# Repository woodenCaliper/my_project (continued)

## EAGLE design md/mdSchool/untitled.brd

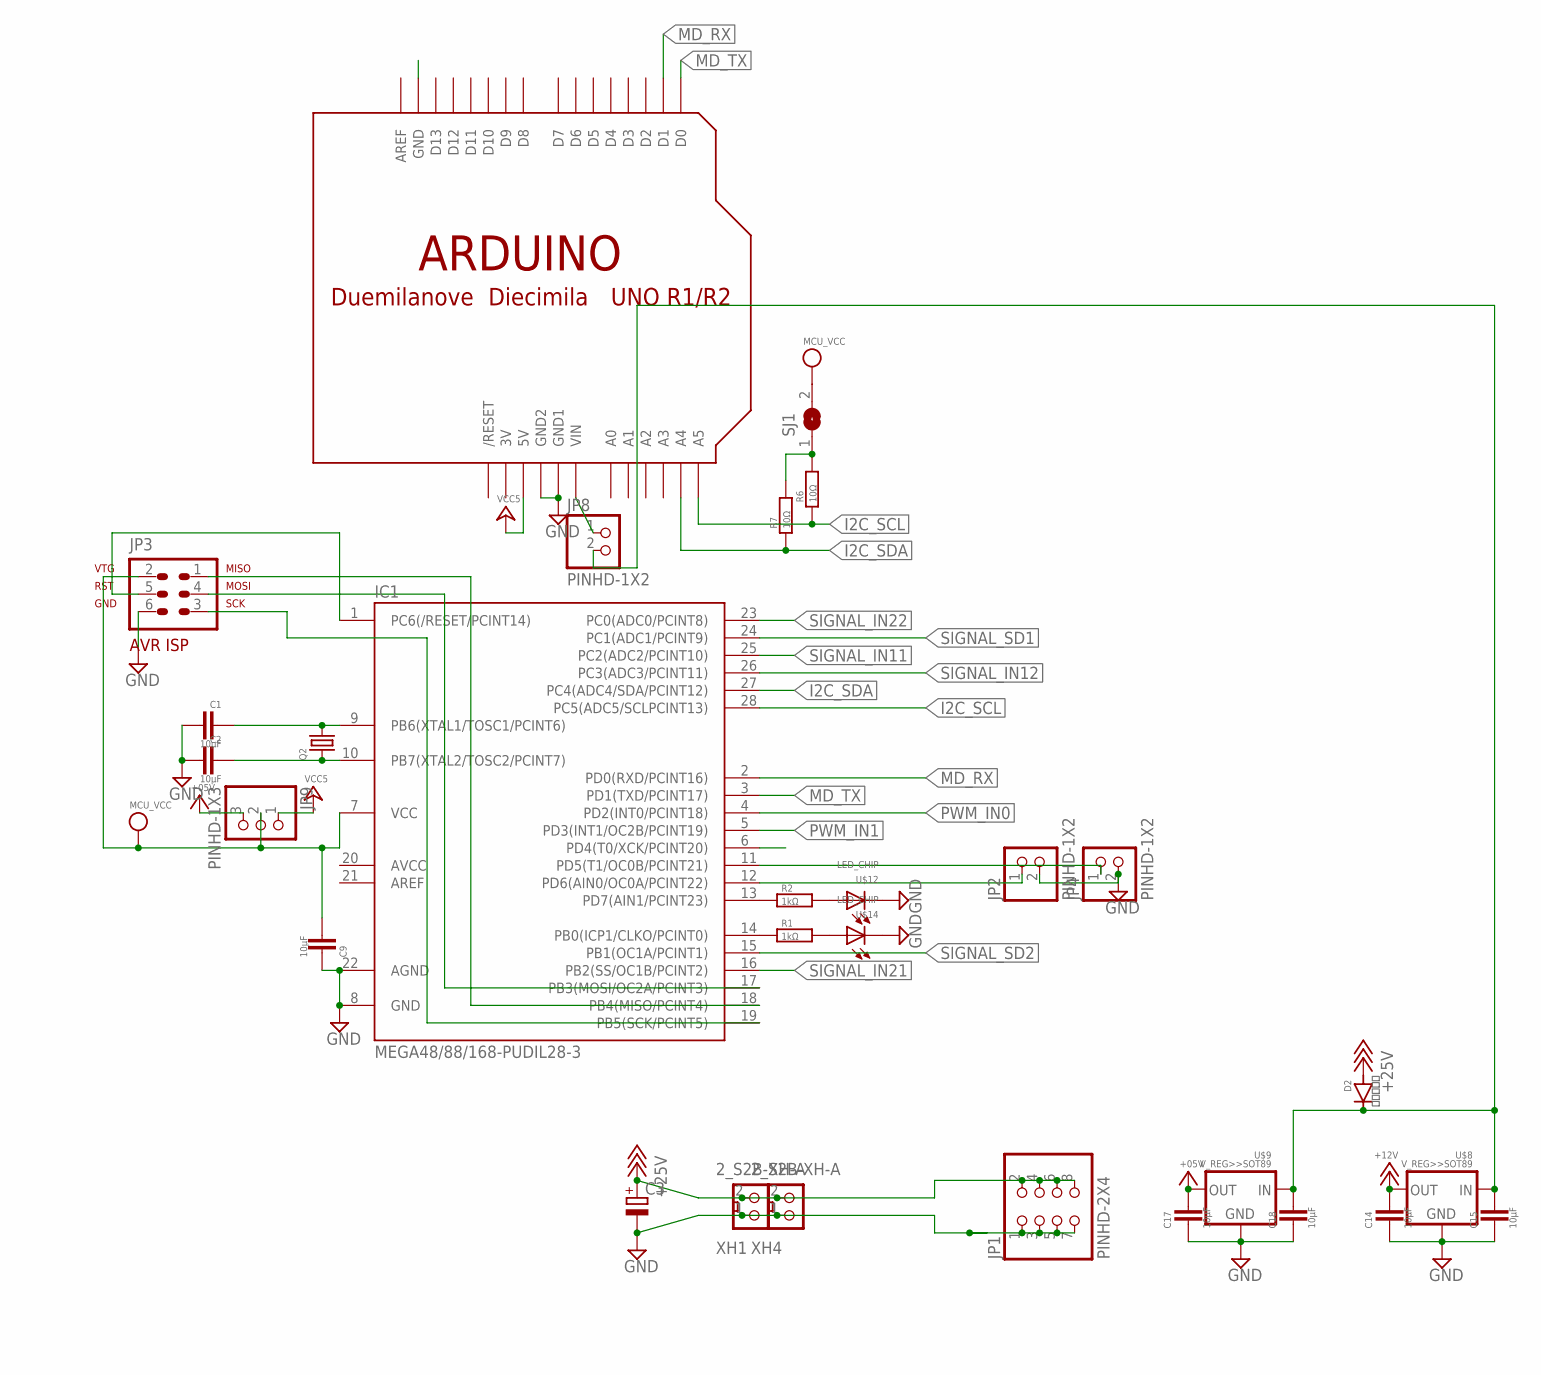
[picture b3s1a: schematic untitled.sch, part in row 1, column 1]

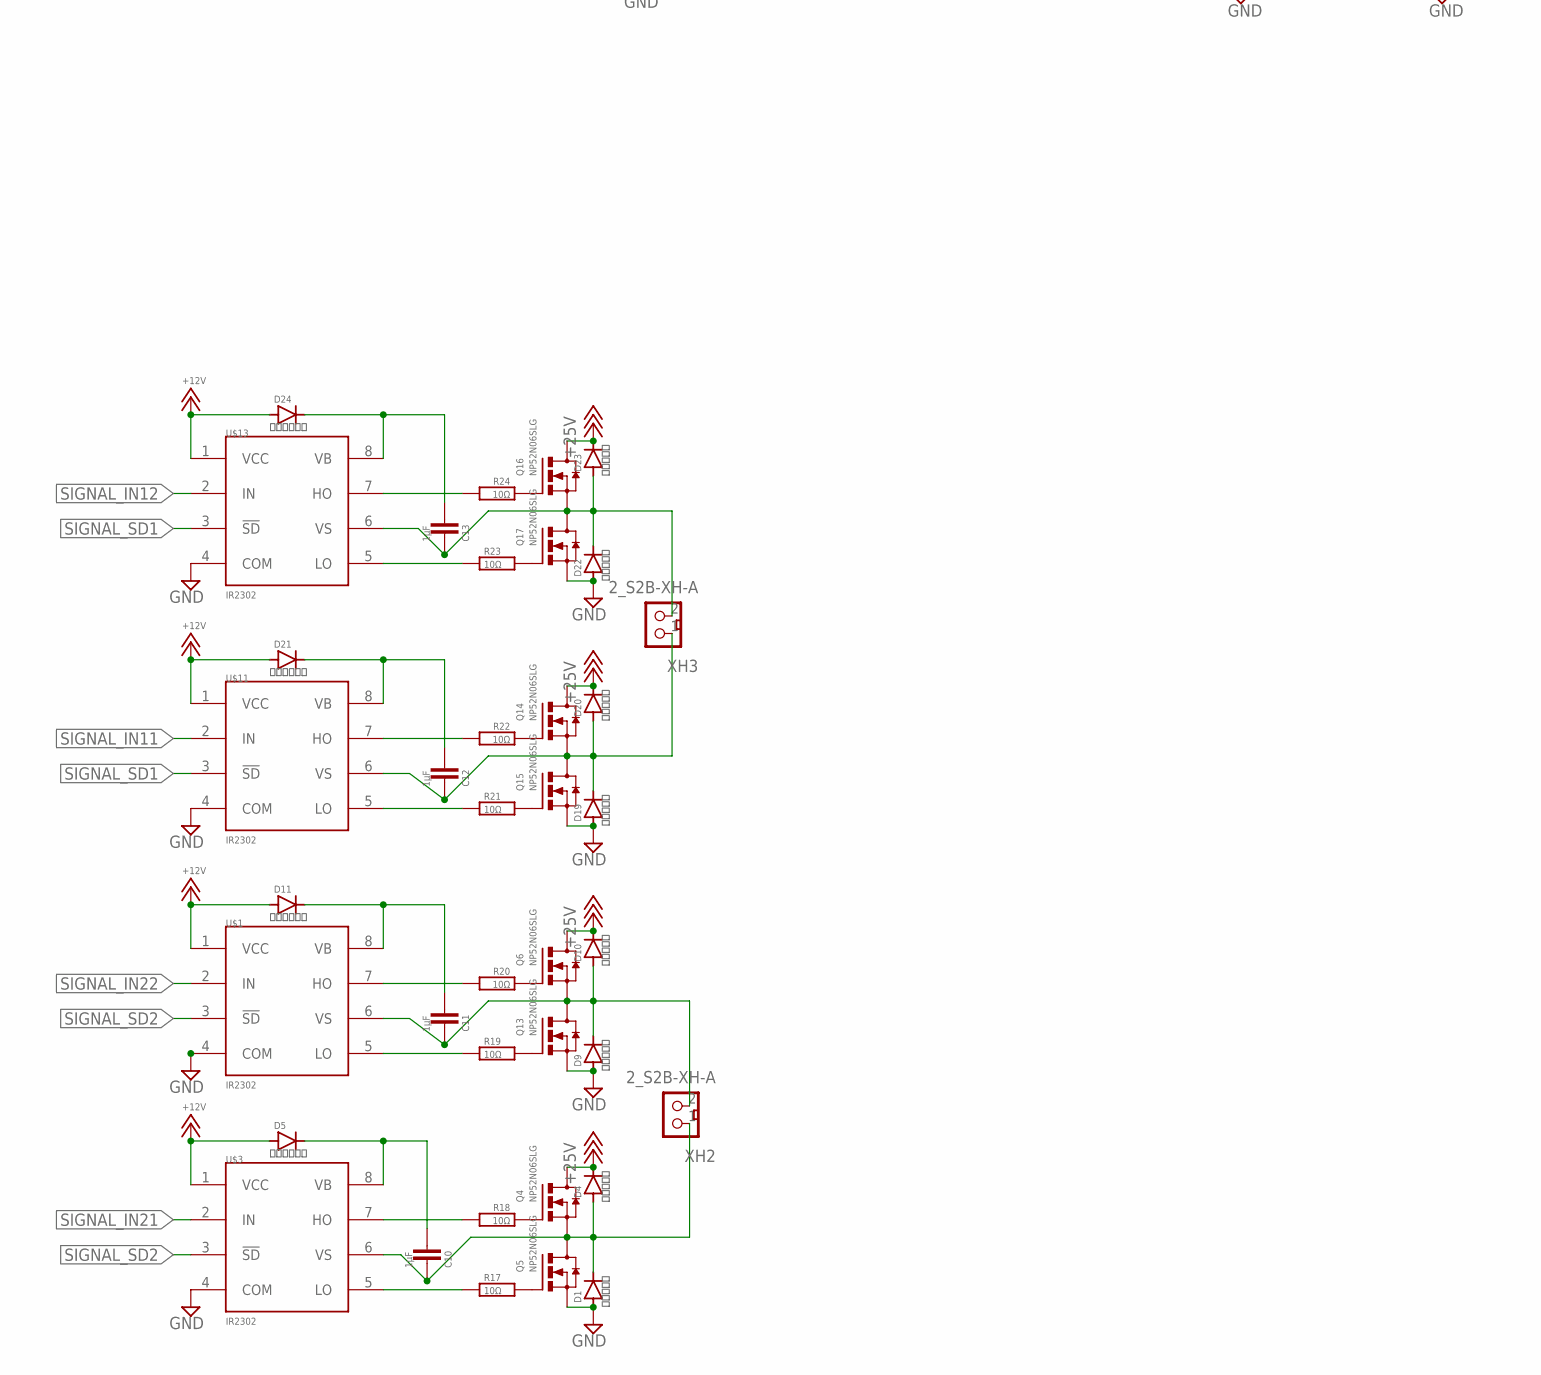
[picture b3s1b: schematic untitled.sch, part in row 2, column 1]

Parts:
C1, C2, C9, C14, C15, C17, C18: 10μF; 2012
C3: CPOL-EUUD-6,3X8,8; UD-6,3X5,8_NICHICON
C10, C11, C12, C13: 1μF; 2012
D1, D2, D4, D9, D10, D19, D20, D22, D23: ＭＳ１８Ｆ; MS18F
D5, D11, D21, D24: ＳＤ１０３Ａ; SOD123
IC1: MEGA48/88/168-PUDIL28-3; DIL28-3
JP1: PINHD-2X4; 2X04
JP2, JP4, JP8: PINHD-1X2; 1X02
JP3: AVR-ISP-6
JP9: PINHD-1X3; 1X03
Q2: CRYSTALHC49S; HC49/S
Q4, Q5, Q6, Q13, Q14, Q15, Q16, Q17: NP52N06SLG; TO252
R1, R2: 1kΩ; 2012
R6, R7, R17, R18, R19, R20, R21, R22, R23, R24: 10Ω; 2012
SJ1: SJ
U$1, U$3, U$11, U$13: IR2302; DIL08
U$2: ARDUINO-NOHOLE
U$8, U$9: V_REG>>SOT89; SOT89
U$12, U$14: LED_CHIP; 2012
XH1, XH2, XH3, XH4: 2_S2B-XH-A; S2B-XH-A

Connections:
3V: U$2.3V
+5V: C17.1, JP9.3, U$9.1 (OUT)
+12V: C14.1, D5.A, D11.A, D21.A, D24.A, U$1.1 (VCC), U$3.1 (VCC), U$8.1 (OUT), U$11.1 (VCC), U$13.1 (VCC)
+18V: C3.+, D2.P$1 (A), D4.P$2 (C), D10.P$2 (C), D20.P$2 (C), D23.P$2 (C), JP1.2, JP1.4, JP1.6, JP1.8, Q4.3 (D), Q6.3 (D), Q14.3 (D), Q16.3 (D), XH1.2, XH4.2
GND: C1.1, C2.1, C3.-, C9.2, C14.2, C15.2, C17.2, C18.2, D1.P$1 (A), D9.P$1 (A), D19.P$1 (A), D22.P$1 (A), IC1.8 (GND), IC1.22 (AGND), JP1.1, JP1.3, JP1.5, JP1.7, JP2.2, JP3.6, JP4.2, Q5.2 (S), Q13.2 (S), Q15.2 (S), Q17.2 (S), U$1.4 (COM), U$2.GND1, U$2.GND2, U$3.4 (COM), U$8.2 (GND), U$8.2.1 (GND), U$9.2 (GND), U$9.2.1 (GND), U$11.4 (COM), U$12.P$2 (C), U$13.4 (COM), U$14.P$2 (C), XH1.1, XH4.1
I2C_SCL: IC1.28 (PC5(ADC5/SCLPCINT13)), R6.1, U$2.A5
I2C_SDA: IC1.27 (PC4(ADC4/SDA/PCINT12)), R7.1, U$2.A4
MD_RX: IC1.2 (PD0(RXD/PCINT16)), U$2.D1
MD_TX: IC1.3 (PD1(TXD/PCINT17)), U$2.D0
unnamed: C15.1, C18.1, D2.P$2 (C), JP8.2, U$8.3 (IN), U$9.3 (IN)
unnamed: JP8.1, U$2.VIN
unnamed: C13.2, D22.P$2 (C), D23.P$1 (A), Q16.2 (S), Q17.3 (D), U$13.6 (VS), XH3.2
unnamed: IC1.14 (PB0(ICP1/CLKO/PCINT0)), R1.1
unnamed: IC1.1 (PC6(/RESET/PCINT14)), JP3.5
unnamed: IC1.12 (PD6(AIN0/OC0A/PCINT22)), JP2.1
unnamed: C1.2, IC1.9 (PB6(XTAL1/TOSC1/PCINT6)), Q2.2
unnamed: C2.2, IC1.10 (PB7(XTAL2/TOSC2/PCINT7)), Q2.1
unnamed: IC1.11 (PD5(T1/OC0B/PCINT21)), JP4.1
unnamed: IC1.13 (PD7(AIN1/PCINT23)), R2.1
unnamed: IC1.19 (PB5(SCK/PCINT5)), JP3.3
unnamed: C11.2, D9.P$2 (C), D10.P$1 (A), Q6.2 (S), Q13.3 (D), U$1.6 (VS), XH2.2
unnamed: R1.2, U$14.P$1 (A)
unnamed: R2.2, U$12.P$1 (A)
unnamed: C10.2, D1.P$2 (C), D4.P$1 (A), Q4.2 (S), Q5.3 (D), U$3.6 (VS), XH2.1
unnamed: Q5.1 (G), R17.2
unnamed: R17.1, U$3.5 (LO)
unnamed: R6.2, R7.2, SJ1.1
unnamed: IC1.17 (PB3(MOSI/OC2A/PCINT3)), JP3.4
unnamed: IC1.18 (PB4(MISO/PCINT4)), JP3.1
unnamed: R18.2, U$3.7 (HO)
unnamed: C10.1, D5.C, U$3.8 (VB)
unnamed: Q4.1 (G), R18.1
unnamed: Q13.1 (G), R19.2
unnamed: R19.1, U$1.5 (LO)
unnamed: R20.2, U$1.7 (HO)
unnamed: C11.1, D11.C, U$1.8 (VB)
unnamed: Q6.1 (G), R20.1
unnamed: C12.2, D19.P$2 (C), D20.P$1 (A), Q14.2 (S), Q15.3 (D), U$11.6 (VS), XH3.1
unnamed: Q15.1 (G), R21.2
unnamed: R21.1, U$11.5 (LO)
unnamed: R22.2, U$11.7 (HO)
unnamed: C12.1, D21.C, U$11.8 (VB)
unnamed: Q14.1 (G), R22.1
unnamed: Q17.1 (G), R23.2
unnamed: R23.1, U$13.5 (LO)
unnamed: R24.2, U$13.7 (HO)
unnamed: C13.1, D24.C, U$13.8 (VB)
unnamed: Q16.1 (G), R24.1
PWM_IN0: IC1.4 (PD2(INT0/PCINT18))
PWM_IN1: IC1.5 (PD3(INT1/OC2B/PCINT19))
SIGNAL_IN11: IC1.25 (PC2(ADC2/PCINT10)), U$11.2 (IN)
SIGNAL_IN12: IC1.26 (PC3(ADC3/PCINT11)), U$13.2 (IN)
SIGNAL_IN21: IC1.16 (PB2(SS/OC1B/PCINT2)), U$3.2 (IN)
SIGNAL_IN22: IC1.23 (PC0(ADC0/PCINT8)), U$1.2 (IN)
SIGNAL_SD1: IC1.24 (PC1(ADC1/PCINT9)), U$11.3 (!SD), U$13.3 (!SD)
SIGNAL_SD2: IC1.15 (PB1(OC1A/PCINT1)), U$1.3 (!SD), U$3.3 (!SD)
VCC: C9.1, IC1.7 (VCC), JP3.2, JP9.2, SJ1.2
VCC5: JP9.1, U$2.5V

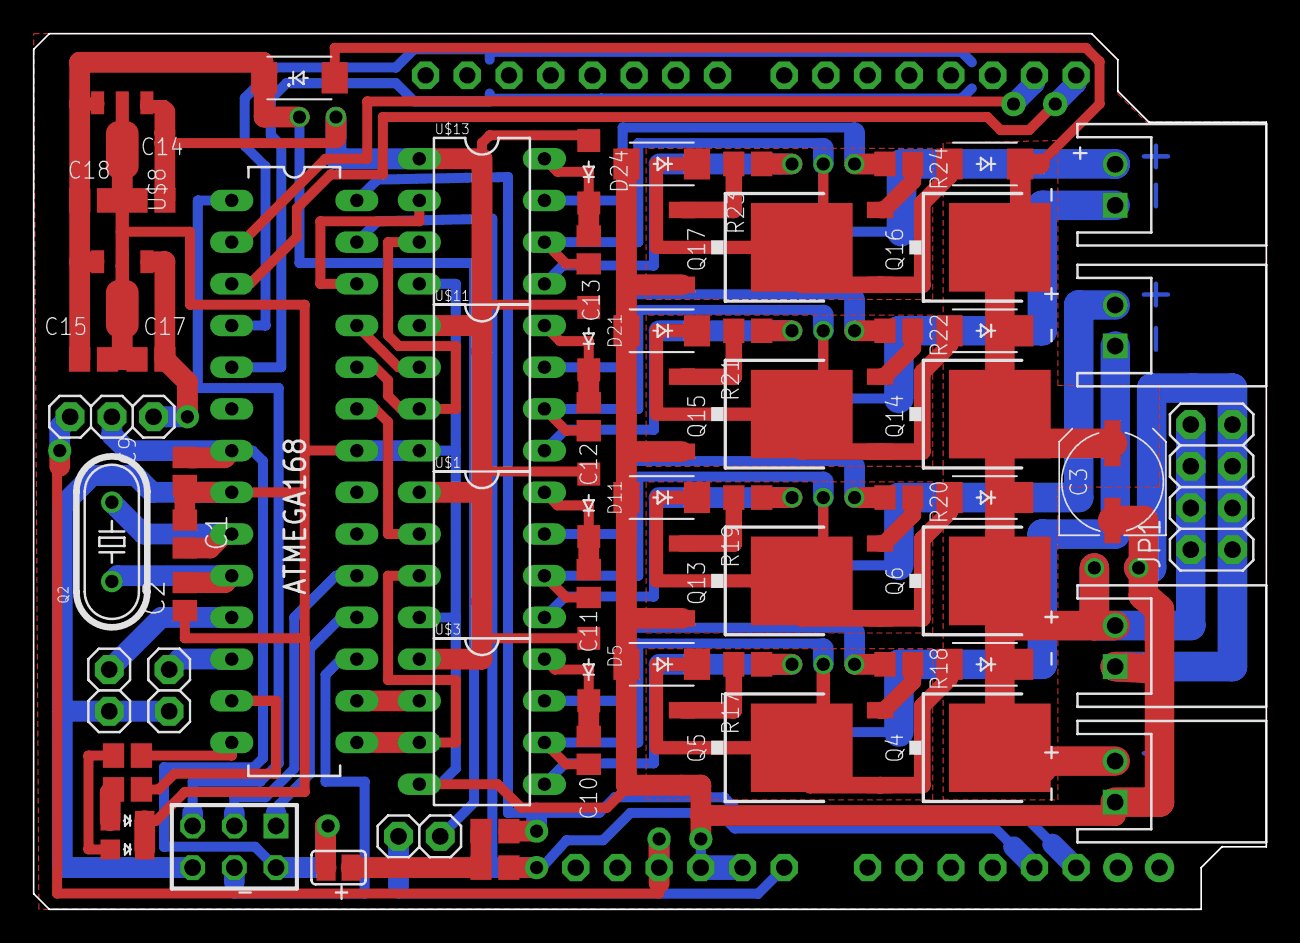
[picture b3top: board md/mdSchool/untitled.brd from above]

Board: 2 copper layers, 75.1 x 53.3 mm, 67 parts (0 on the bottom side), 55 nets.

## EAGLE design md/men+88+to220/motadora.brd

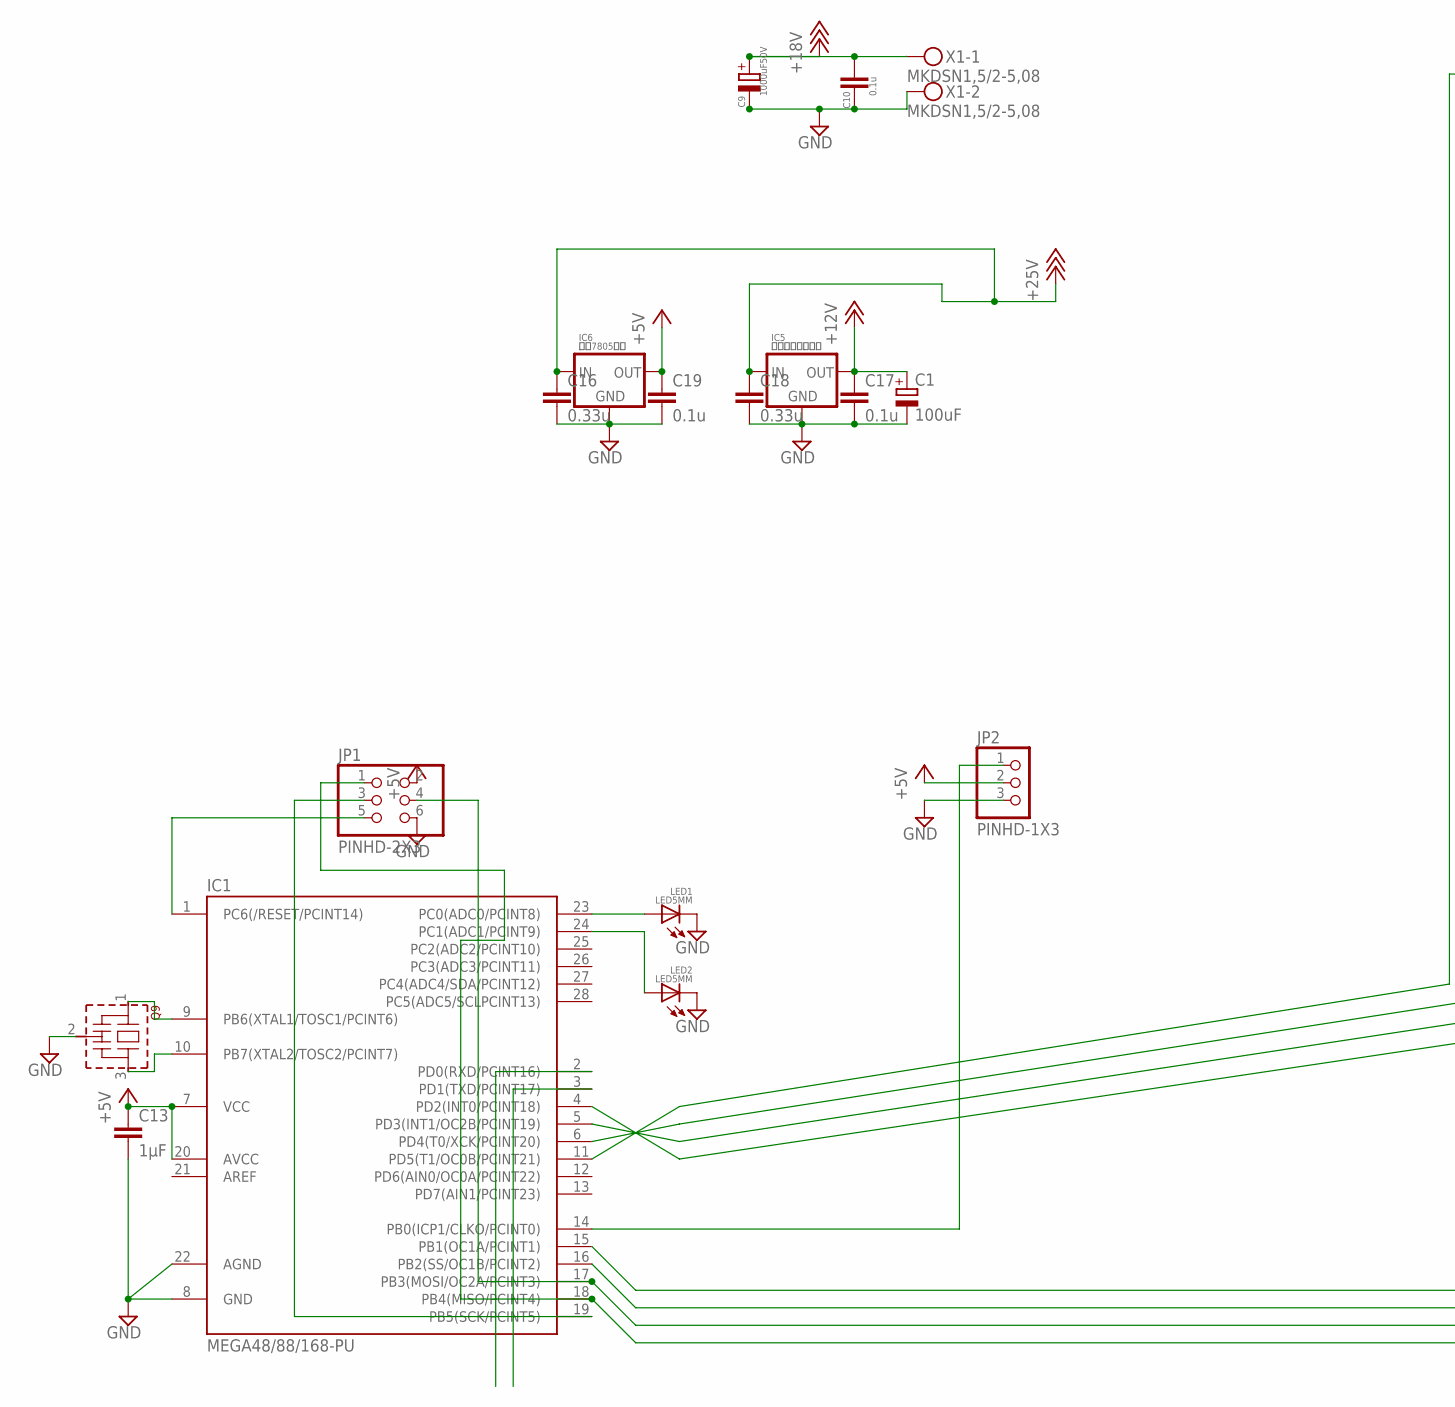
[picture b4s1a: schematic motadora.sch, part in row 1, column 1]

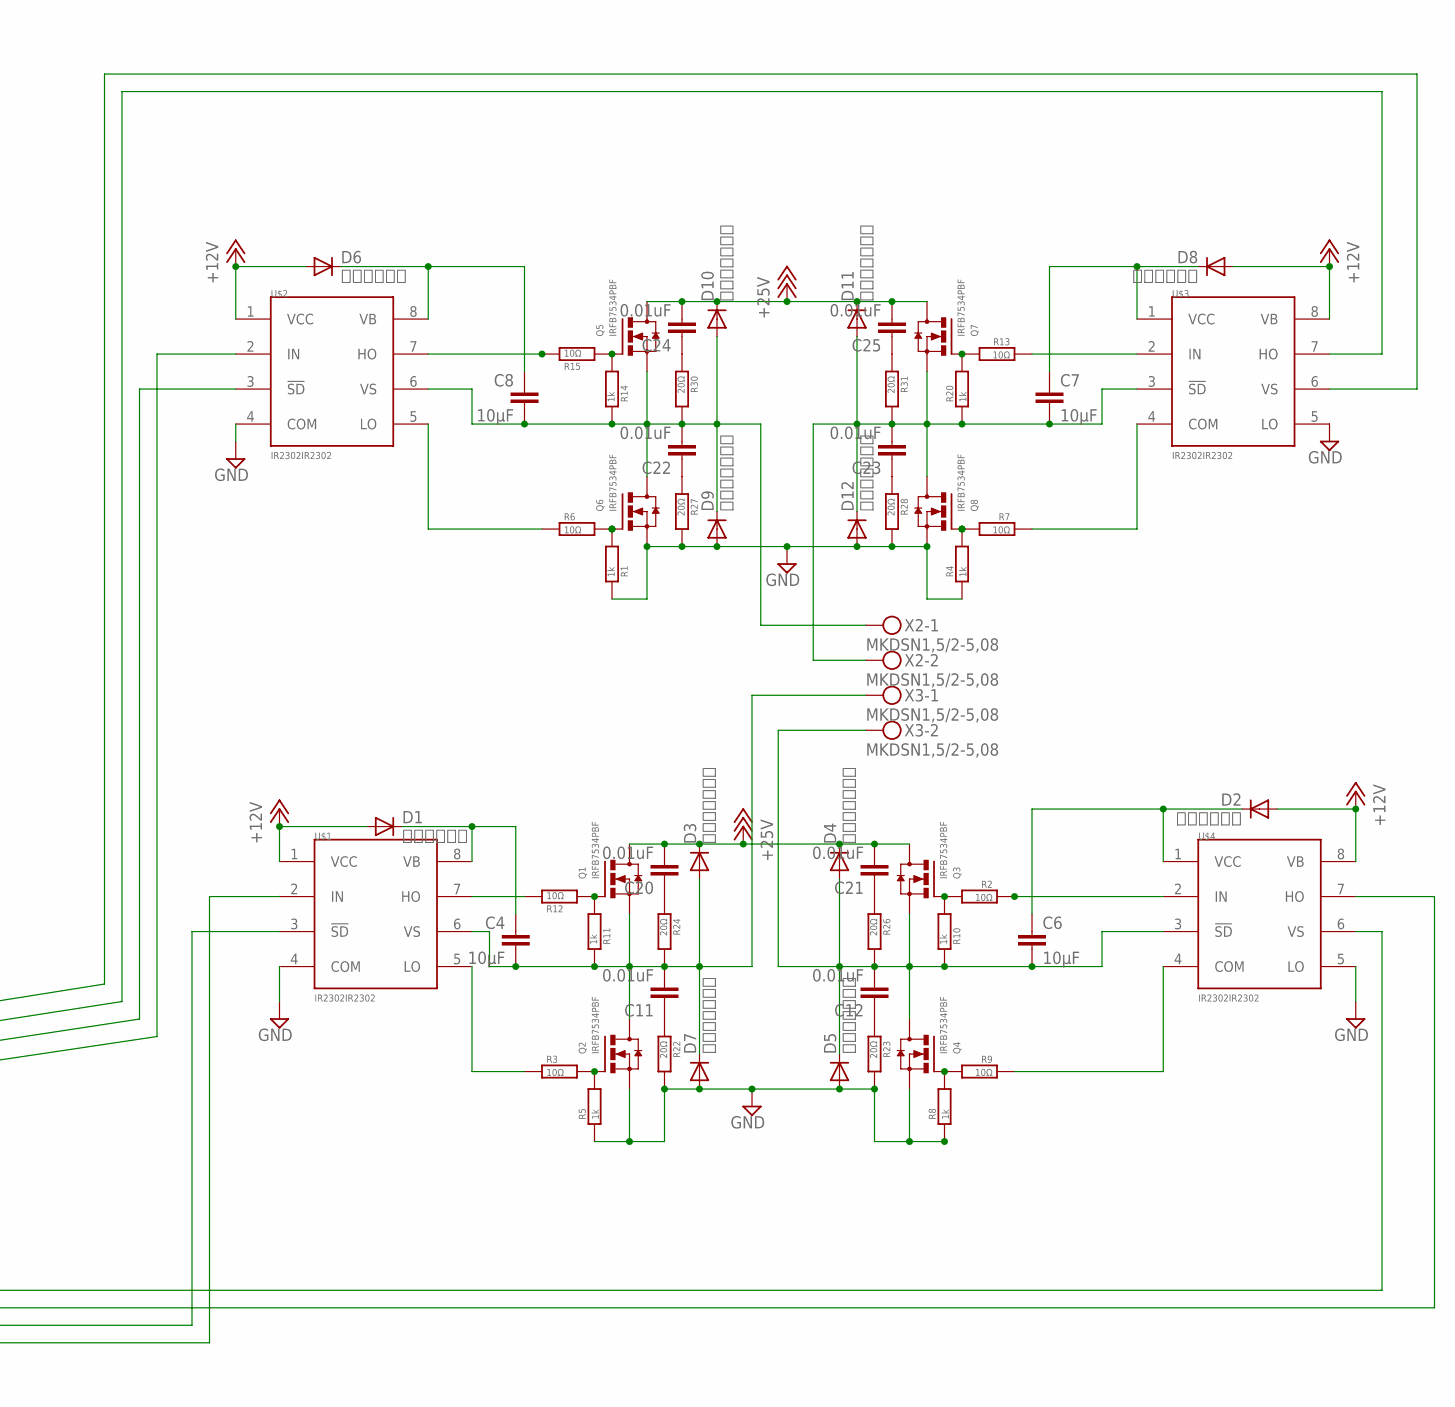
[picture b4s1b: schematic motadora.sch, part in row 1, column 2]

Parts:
C1: 100uF; TT2D6
C4, C6, C7, C8: 10μF; C025-025X050
C9: 1000uF50V; E2,5-7
C10, C17, C19: 0.1u; C025-025X050
C11, C12, C20, C21, C22, C23, C24, C25: 0.01uF; C025-024X044
C13: 1μF; C050-025X075
C16, C18: 0.33u; C025-025X050
D1, D2, D6, D8: ＳＤ１０３Ａ; D-5
D3, D4, D5, D7, D9, D10, D11, D12: １１ＥＱＳ０６; D-5
IC1: MEGA48/88/168-PU; DIL28-3
IC5: ＬＭ７８１２ＣＶ; TO-92
IC6: ＬＭ7805ＣＶ; TO-92
JP1: PINHD-2X3; 2X03
JP2: PINHD-1X3; 1X03
LED1, LED2: LED5MM
Q1, Q2, Q3, Q4, Q5, Q6, Q7, Q8: IRFB7534PBF; TO220_2
Q9: CSTLS_X
R1, R4, R5, R8, R10, R11, R14, R20: 1k; 1/4W(8MM)
R2, R3, R6, R7, R9, R12, R13, R15: 10Ω; 1/4W(2.5MM)_
R22, R23, R24, R26, R27, R28, R30, R31: 20Ω; 1/4W(2.5MM)_
U$1, U$2, U$3, U$4: IR2302IR2302; DIL08
X1, X2, X3: MKDSN1,5/2-5,08

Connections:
+5V: C13.1, C19.1, IC1.7 (VCC), IC1.20 (AVCC), IC6.3 (OUT), JP1.2, JP2.2
+12V: C1.+, C17.1, D1.A, D2.A, D6.A, D8.A, IC5.3 (OUT), U$1.1 (VCC), U$2.1 (VCC), U$3.8 (VB), U$4.8 (VB)
+18V: C9.+, C10.1, C16.1, C18.1, C20.2, C21.2, C24.2, C25.2, D3.C, D4.C, D10.C, D11.C, IC5.1 (IN), IC6.1 (IN), Q1.2 (D), Q3.2 (D), Q5.2 (D), Q7.2 (D), X1.1
AGND: IC1.22 (AGND)
GND: C1.-, C9.-, C10.2, C13.2, C16.2, C17.2, C18.2, C19.2, D5.A, D7.A, D9.A, D12.A, IC1.8 (GND), IC5.2 (GND), IC6.2 (GND), JP1.6, JP2.3, LED1.K (C), LED2.K (C), Q2.3 (S), Q4.3 (S), Q6.3 (S), Q8.3 (S), Q9.2 (VSS), R1.1, R4.1, R5.1, R8.1, R22.4 (2), R23.4 (2), R27.4 (2), R28.4 (2), U$1.4 (COM), U$2.4 (COM), U$3.5 (LO), U$4.5 (LO), X1.2
unnamed: R15.3 (1), U$2.7 (HO)
unnamed: R13.3 (1), U$3.2 (IN)
unnamed: R12.3 (1), U$1.7 (HO)
unnamed: Q2.1 (G), R3.4 (2), R5.2
unnamed: IC1.10 (PB7(XTAL2/TOSC2/PCINT7)), Q9.3
unnamed: R6.3 (1), U$2.5 (LO)
unnamed: Q1.1 (G), R11.2, R12.4 (2)
unnamed: C4.2, C11.2, D3.A, D7.C, Q1.3 (S), Q2.2 (D), R11.1, R24.4 (2), U$1.6 (VS), X3.1
unnamed: C4.1, D1.C, U$1.8 (VB)
unnamed: C6.1, D2.C, U$4.1 (VCC)
unnamed: R3.3 (1), U$1.5 (LO)
unnamed: C7.1, D8.C, U$3.1 (VCC)
unnamed: Q5.1 (G), R14.2, R15.4 (2)
unnamed: C6.2, C12.2, D4.A, D5.C, Q3.3 (S), Q4.2 (D), R10.1, R26.4 (2), U$4.3 (!SD), X3.2
unnamed: C8.1, D6.C, U$2.8 (VB)
unnamed: Q4.1 (G), R8.2, R9.4 (2)
unnamed: IC1.14 (PB0(ICP1/CLKO/PCINT0)), JP2.1
unnamed: C7.2, C23.2, D11.A, D12.C, Q7.3 (S), Q8.2 (D), R20.1, R31.4 (2), U$3.3 (!SD), X2.2
unnamed: IC1.17 (PB3(MOSI/OC2A/PCINT3)), JP1.4, U$1.3 (!SD)
unnamed: Q6.1 (G), R1.2, R6.4 (2)
unnamed: IC1.9 (PB6(XTAL1/TOSC1/PCINT6)), Q9.1
unnamed: IC1.15 (PB1(OC1A/PCINT1)), U$4.6 (VS)
unnamed: IC1.5 (PD3(INT1/OC2B/PCINT19)), U$2.3 (!SD)
unnamed: Q8.1 (G), R4.2, R7.4 (2)
unnamed: C8.2, C22.2, D9.C, D10.A, Q5.3 (S), Q6.2 (D), R14.1, R30.4 (2), U$2.6 (VS), X2.1
unnamed: IC1.16 (PB2(SS/OC1B/PCINT2)), U$4.7 (HO)
unnamed: IC1.23 (PC0(ADC0/PCINT8)), LED1.A
unnamed: IC1.24 (PC1(ADC1/PCINT9)), LED2.A
unnamed: C12.1, R23.3 (1)
unnamed: C11.1, R22.3 (1)
unnamed: Q3.1 (G), R2.4 (2), R10.2
unnamed: R7.3 (1), U$3.4 (COM)
unnamed: IC1.6 (PD4(T0/XCK/PCINT20)), U$3.7 (HO)
unnamed: C20.1, R24.3 (1)
unnamed: C21.1, R26.3 (1)
unnamed: C22.1, R27.3 (1)
unnamed: C23.1, R28.3 (1)
unnamed: C24.1, R30.3 (1)
unnamed: C25.1, R31.3 (1)
unnamed: R2.3 (1), U$4.2 (IN)
unnamed: IC1.11 (PD5(T1/OC0B/PCINT21)), U$3.6 (VS)
unnamed: IC1.18 (PB4(MISO/PCINT4)), JP1.1, U$1.2 (IN)
unnamed: Q7.1 (G), R13.4 (2), R20.2
unnamed: IC1.4 (PD2(INT0/PCINT18)), U$2.2 (IN)
unnamed: R9.3 (1), U$4.4 (COM)
unnamed: IC1.19 (PB5(SCK/PCINT5)), JP1.3
unnamed: IC1.1 (PC6(/RESET/PCINT14)), JP1.5

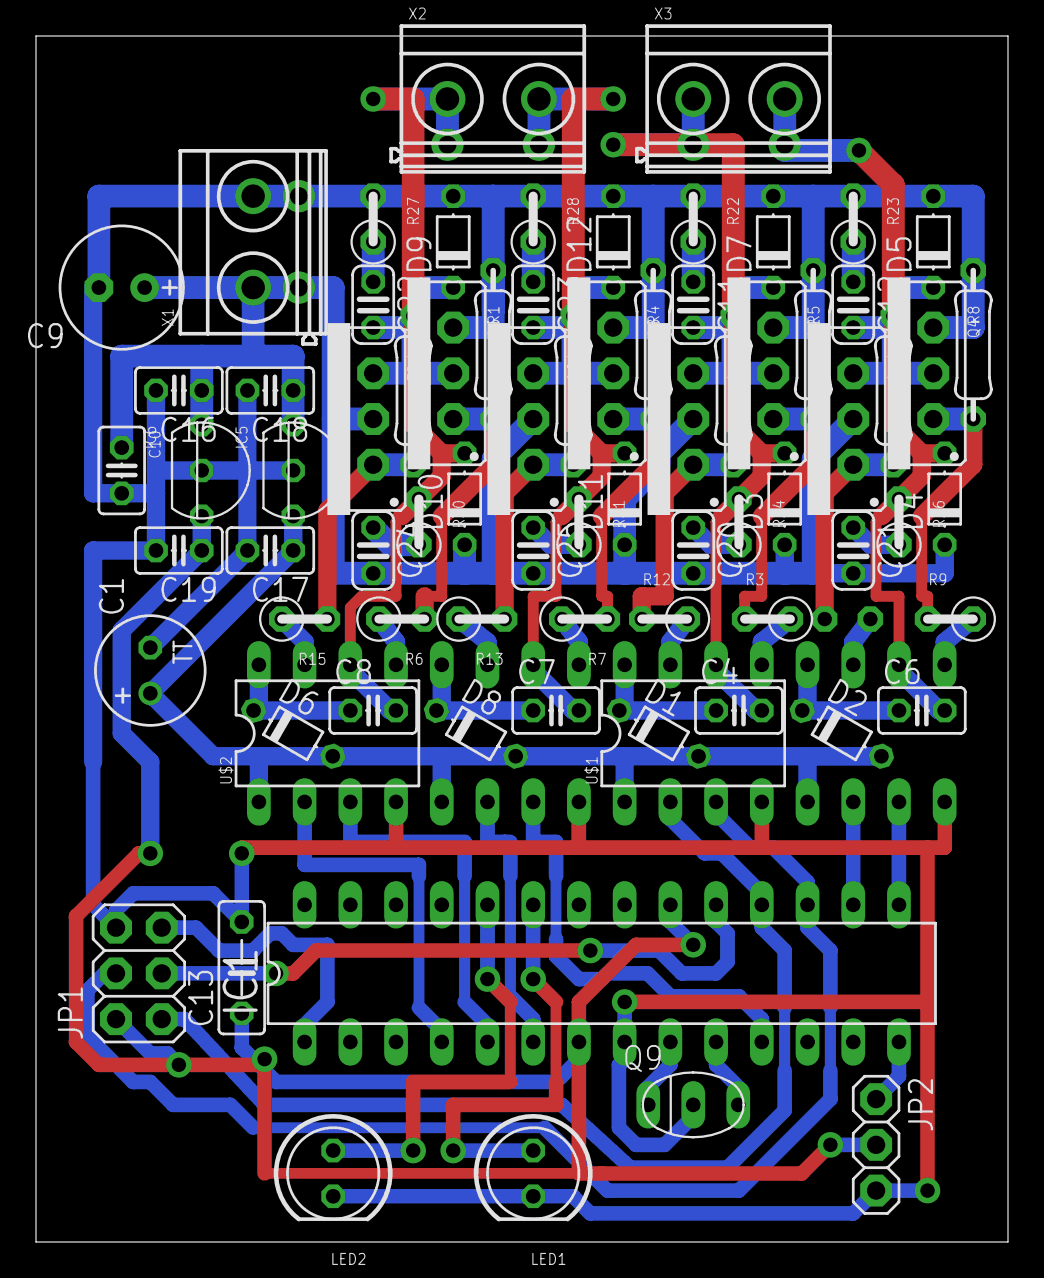
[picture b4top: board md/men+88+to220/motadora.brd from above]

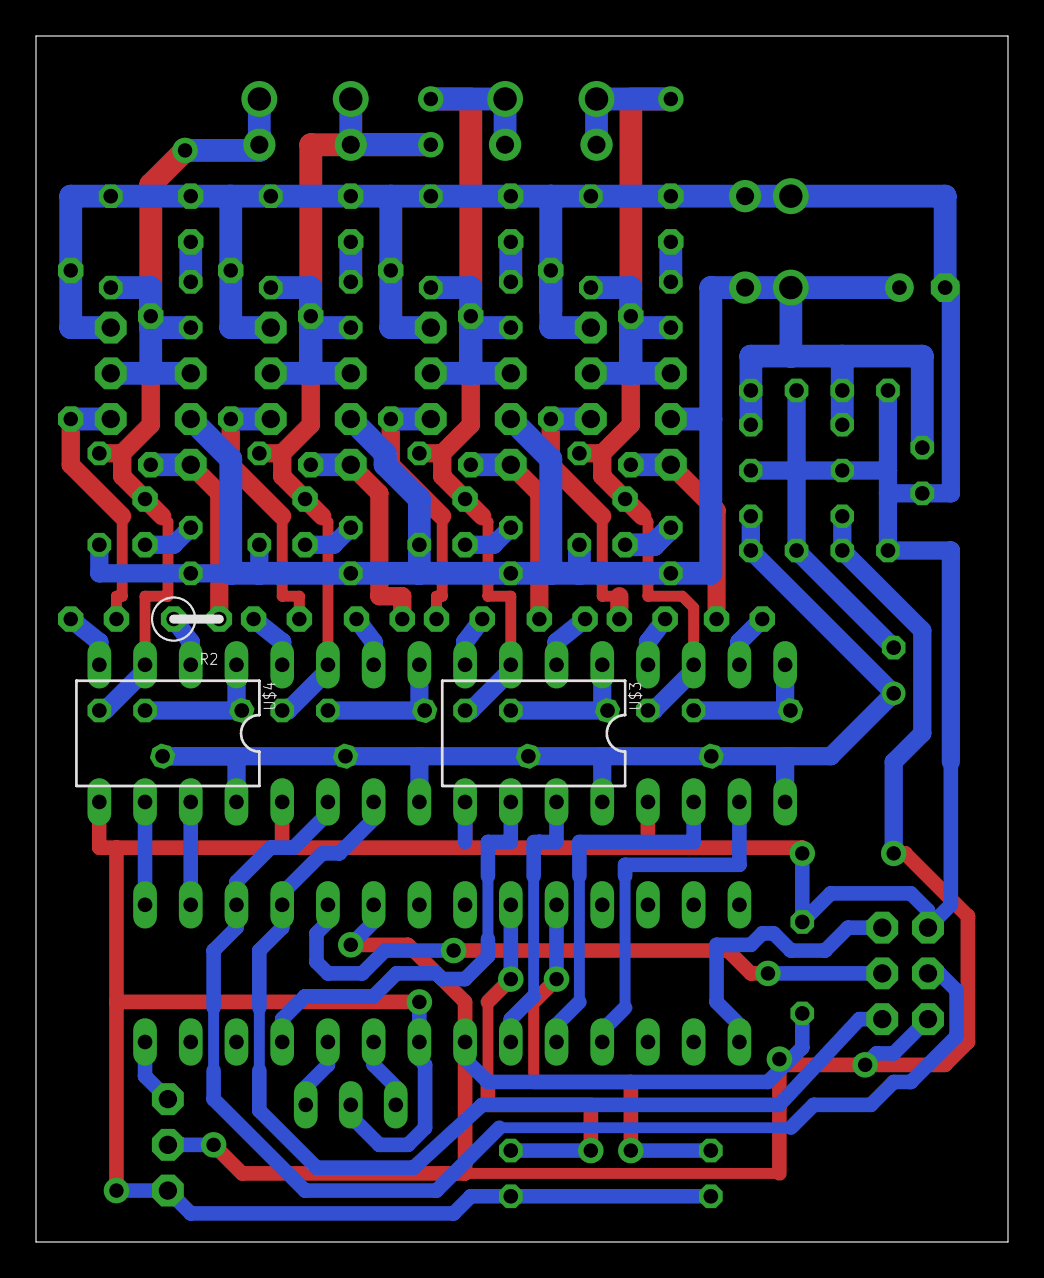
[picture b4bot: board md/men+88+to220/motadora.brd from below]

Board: 2 copper layers, 54.0 x 67.0 mm, 79 parts (3 on the bottom side), 51 nets.

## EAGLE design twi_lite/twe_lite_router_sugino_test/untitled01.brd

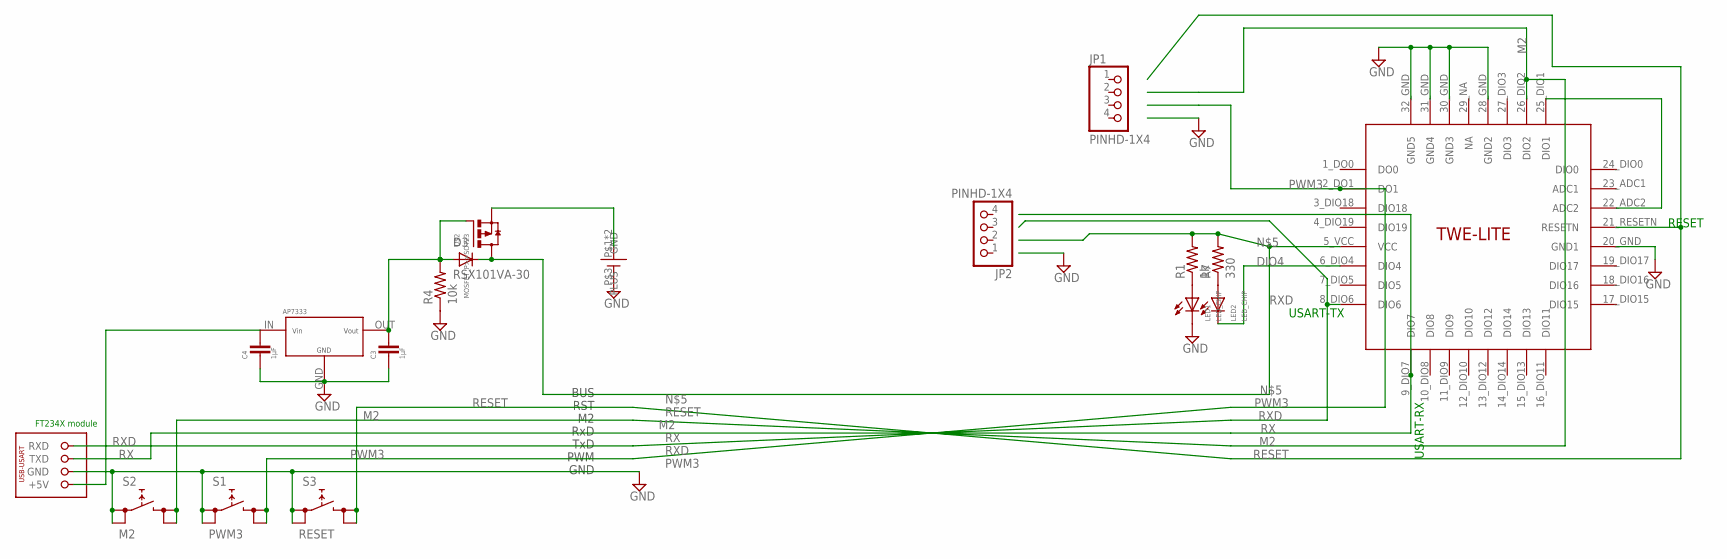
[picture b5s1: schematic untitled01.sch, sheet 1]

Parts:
C3, C4: 1μF; C2012
D3: RSX101VA-30; RSX101VA
JP1, JP2: PINHD-1X4; 1X04
LED1, LED2: LED_CHIP; 2012
R1: 1k; R0805
R4: 10k; M0805
R7: 330; R0805
S1: PWM3; LS6
S2: M2; LS6
S3: RESET; LS6
U$1: STL2477HLD-A
U$2: MOSFET_P>>SOT23; SOT23
U$3: AE-FT234X
U$4: AP7333_SOT-23
U$5: TWE-001L

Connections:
3.3V_1: C3.1, D3.ANODE (A), R4.2, U$2.1 (G), U$4.OUT
BUS_POWER: C4.1, U$3.P$1 (+5V), U$4.IN
DIO4: LED2.P$2 (C), U$5.6_DIO4 (DIO4)
DIO7: U$5.9_DIO7 (DIO7)
GND: LED1.P$2 (C), S1.P$1 (0), S1.P$2 (0), S2.P$1 (0), S2.P$2 (0), S3.P$1 (0), S3.P$2 (0), U$1.P$3 (GND), U$3.P$2 (GND), U$5.20_GND (GND1), U$5.28_GND (GND2), U$5.30_GND (GND3), U$5.31_GND (GND4), U$5.32_GND (GND5)
GND_1: C3.2, C4.2, R4.1, U$4.GND
M2: S2.P$3 (1), S2.P$4 (1), U$5.26_DIO2 (DIO2)
unnamed: LED2.P$1 (A), R7.1
unnamed: LED1.P$1 (A), R1.1
unnamed: D3.CATHODE (C), R1.2, R7.2, U$2.3 (D), U$5.5_VCC (VCC)
unnamed: U$5.22_ADC2 (ADC2), U$5.25_DIO1 (DIO1)
PLUS: U$1.P$1 (PLUS), U$1.P$2 (PLUS), U$2.2 (S)
PWM3: S1.P$3 (1), S1.P$4 (1), U$5.2_DO1 (DO1)
RESET: S3.P$3 (1), S3.P$4 (1), U$5.21_RESETN (RESETN)
RX: U$3.P$3 (TXD)
RXD: U$3.P$4 (RXD), U$5.8_DIO6 (DIO6)

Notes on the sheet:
USART-RX
USART-TX
RESET
FT234X module
GND
PWM
TxD
RxD
RST
BUS

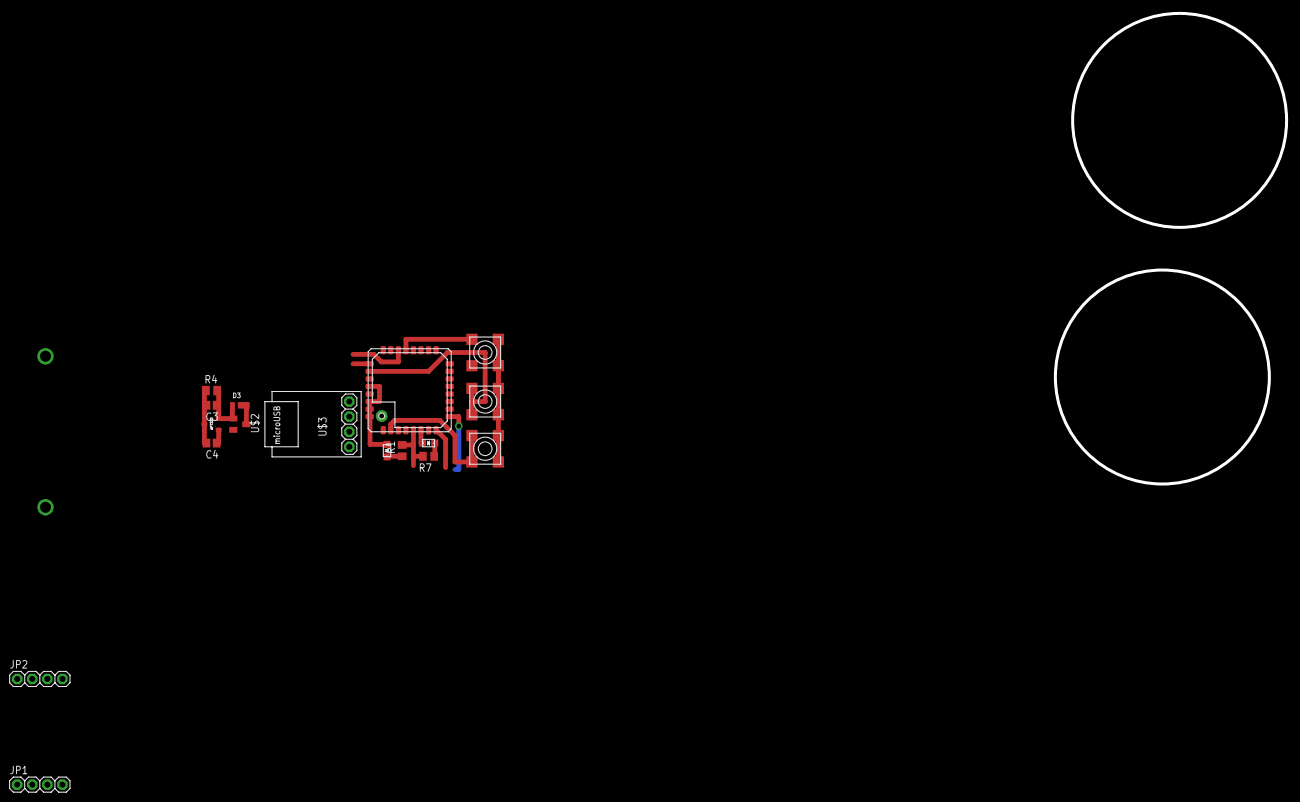
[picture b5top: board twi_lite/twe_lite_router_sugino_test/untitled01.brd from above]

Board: 2 copper layers, 38.9 x 79.2 mm, 18 parts (1 on the bottom side), 14 nets.

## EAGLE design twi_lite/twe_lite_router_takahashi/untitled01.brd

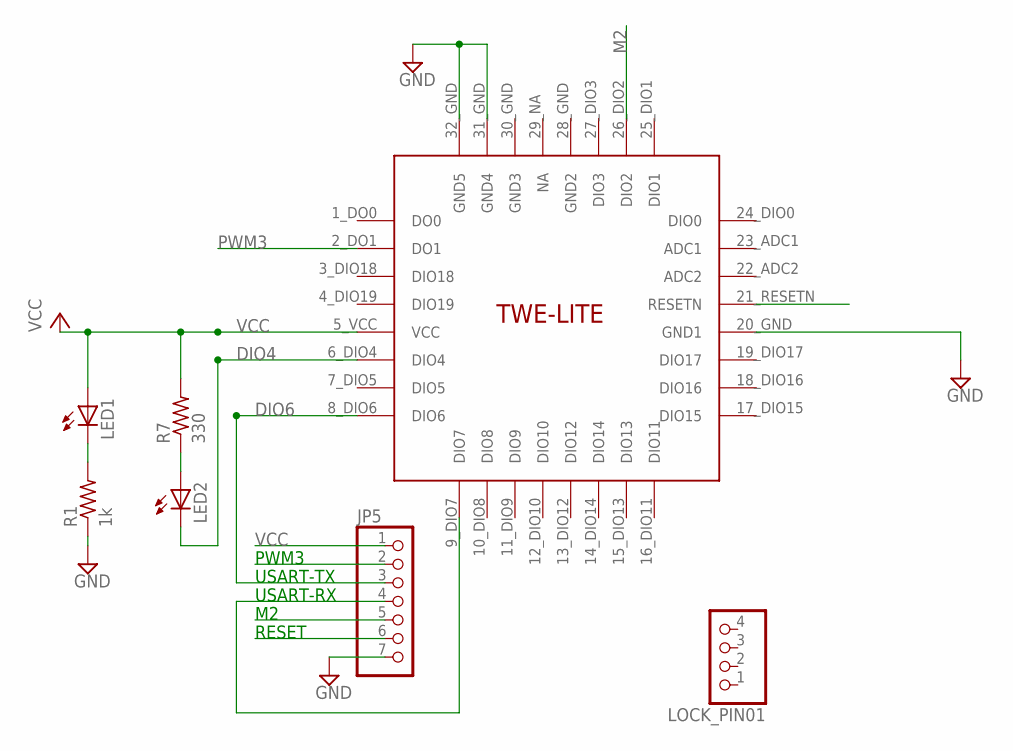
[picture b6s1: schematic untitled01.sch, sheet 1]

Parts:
JP5: PINHD-1X7; 1X07
LED1, LED2: LEDCHIP-LED0603; CHIP-LED0603
LOCK_PIN01: PINHD-1X4; 1X04
R1: 1k; R0805
R7: 330; R0805
U$5: TWE-001L

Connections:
DIO4: LED2.C, U$5.6_DIO4 (DIO4)
DIO6: JP5.3, U$5.8_DIO6 (DIO6)
DIO7: JP5.4, U$5.9_DIO7 (DIO7)
GND: JP5.7, R1.1, U$5.20_GND (GND1), U$5.31_GND (GND4), U$5.32_GND (GND5)
M2: JP5.5, U$5.26_DIO2 (DIO2)
unnamed: LED2.A, R7.1
unnamed: LED1.C, R1.2
PWM3: JP5.2, U$5.2_DO1 (DO1)
RESET: JP5.6, U$5.21_RESETN (RESETN)
VCC: JP5.1, LED1.A, R7.2, U$5.5_VCC (VCC)

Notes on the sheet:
USART-RX
USART-TX
RESET
PWM3

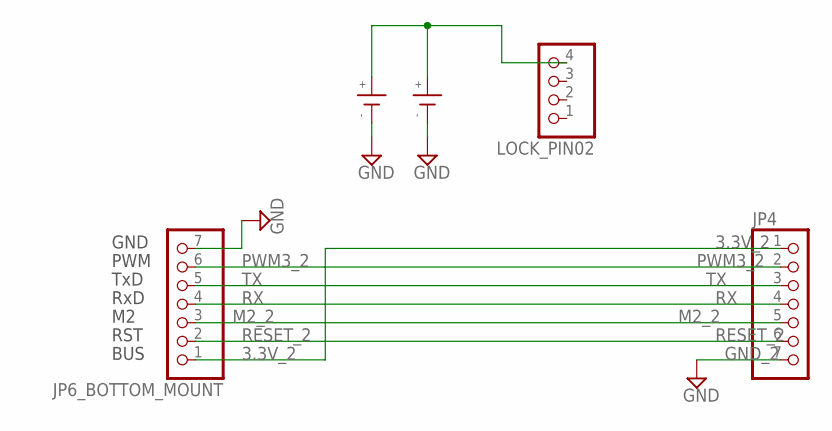
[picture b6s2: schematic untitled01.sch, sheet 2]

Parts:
JP4, JP6_BOTTOM_MOUNT: PINHD-1X7; 1X07
LOCK_PIN02: PINHD-1X4; 1X04
U$2, U$3: CH004-2032LF

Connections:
3.3V_2: JP4.1, JP6_BOTTOM_MOUNT.1
BATTERY_2: LOCK_PIN02.4, U$2.+, U$3.+
GND_2: JP4.7, JP6_BOTTOM_MOUNT.7, U$2.-, U$3.-
M2_2: JP4.5, JP6_BOTTOM_MOUNT.3
PWM3_2: JP4.2, JP6_BOTTOM_MOUNT.6
RESET_2: JP4.6, JP6_BOTTOM_MOUNT.2
RX: JP4.4, JP6_BOTTOM_MOUNT.4
TX: JP4.3, JP6_BOTTOM_MOUNT.5

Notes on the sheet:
GND
PWM
TxD
RxD
RST
BUS

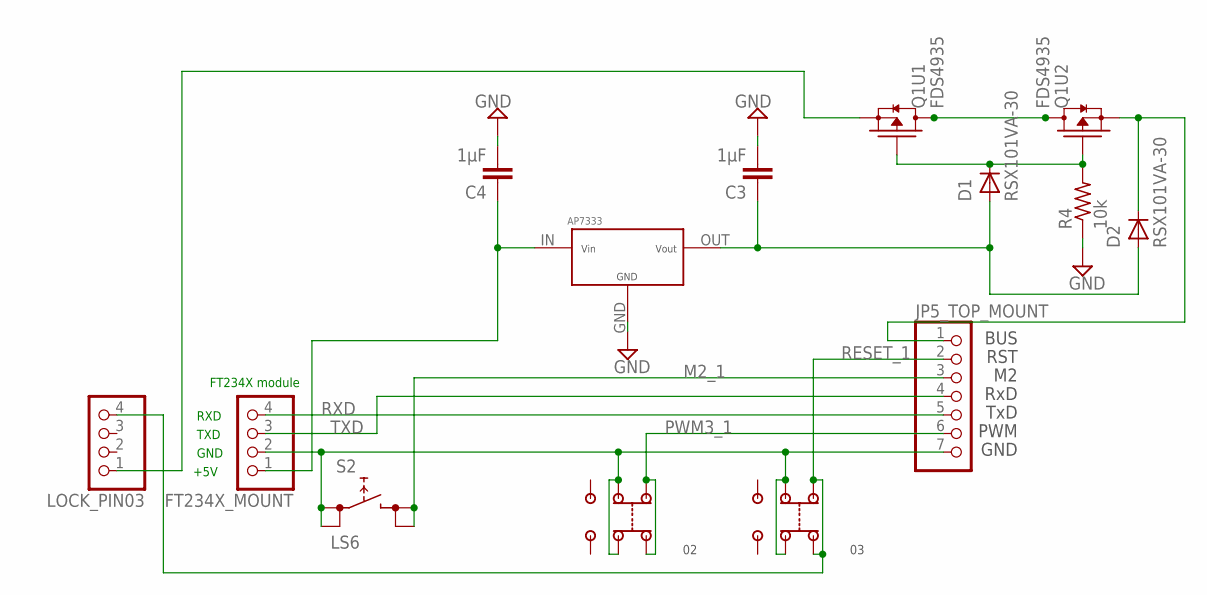
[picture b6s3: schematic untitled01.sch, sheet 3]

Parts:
02, 03: SSSS213202
C3, C4: 1μF; C1608
D1, D2: RSX101VA-30; RSX101VA
FT234X_MOUNT: PINHD-1X4; 1X04
JP5_TOP_MOUNT: PINHD-1X7; 1X07
LOCK_PIN03: PINHD-1X4; 1X04
Q1: FDS4935; SOIC(8PIN)
R4: 10k; M0805
S2: LS6
U$4: AP7333_SOT-23

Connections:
3.3V_1: C3.1, D1.ANODE (A), D2.ANODE (A), U$4.OUT
BATTERY_1: LOCK_PIN03.1, Q1.1 (S)
BUS_POWER: C4.1, FT234X_MOUNT.1, U$4.IN
GND_1: 02.2-1, 02.2-2, 03.2-1, 03.2-2, C3.2, C4.2, FT234X_MOUNT.2, JP5_TOP_MOUNT.7, R4.1, S2.P$1 (0), S2.P$2 (0), U$4.GND
M2_1: JP5_TOP_MOUNT.3, S2.P$3 (1), S2.P$4 (1)
unnamed: D1.CATHODE (C), Q1.2 (G), Q1.4 (G), R4.2
unnamed: Q1.5 (D2), Q1.6 (D1), Q1.7 (D2), Q1.8 (D1)
PWM3_1: 02.1-1, 02.1-2, JP5_TOP_MOUNT.6
RESET_1: 03.1-1, 03.1-2, JP5_TOP_MOUNT.2, LOCK_PIN03.4
RXD: FT234X_MOUNT.4, JP5_TOP_MOUNT.5
TXD: FT234X_MOUNT.3, JP5_TOP_MOUNT.4
VCC_1: D2.CATHODE (C), JP5_TOP_MOUNT.1, Q1.3 (S)

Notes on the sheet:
+5V
GND
TXD
RXD
FT234X module
PWM
TxD
RxD
RST
BUS
